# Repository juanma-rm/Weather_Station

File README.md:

# Weather Station
Weather Station is a system that senses temperature and humidity and allows checking them via Blynk (from Android app, for instance).

It is based on:
  - Wemos D1 mini ESP8266-based board, taking charge of requesting data from the sensor and sending it to a Blynk server via Wi-Fi. The device sends data for 4 seconds and goes in deep sleep mode for 5 minutes to save power.
  - DHT22 temperature and humidity sensor.
  - Blynk server to host the data.

The hardware and software diagrams, as well as the 3D view of the resulting PCB, may be found below:

* Note: Several (N) systems may be used to sense data at different points, each one requiring one DHT22 and one Wemos D1 mini
<br/>
<br/>

# Requirements
- 1 Wemos D1 mini per node
- 1 DHT22 per node
- 1 10kOhm resistor per node
- 1 microUSB charger per node
- Some way to tie and put all the previous components together (PCB + solder kit, protoboard + wires, ...)
- Blynk account + Blynk client (Android app, for instance)
- Wi-Fi available for Wemos D1 mini

# Instructions (based on my developments tools)
1) Software:
    
    1.1) Install VSCode + PlatformIO + Arduino framework + dependencies
          
          lib_deps = blynkkk/Blynk@^1.0.1<br/>
          adafruit/DHT sensor library@^1.4.2<br/>
          adafruit/Adafruit Unified Sensor@^1.1.4

    1.2) Install some Blynk client (Android app for instance), create a Blynk account and crEate your Blynk project: adding charts, labels or any other elements, creating a new device per each node selecting Wemos D1 mini, generating a token per each node and associating each charts / labels to virtual pins the devices previously created (V1 for temperature, V2 for humidity; this may be changed in main.cpp). Check out Blynk official documentation to get more details.
    
    1.3) Connect the Wemos board (without connecting it to the rest of elements).
    
    1.4) Write your device's Blynk token in auth variable, one token per node; write your WiFi credentials (ssid / pass). DEBUG macro may be uncommented to help in debugging process, if needed.
    
    1.5) Build the main.cpp (dependencies will be automatically compiled) and upload the resulting project to the board.

2) Build the hardware system:

    2.1) Order or build the PCB
    
    2.2) Mount / solder the componentes
    
    2.3) Connect the Micro-USB

3) Enjoy. If all went well, data should be now visible from the Blynk client.

# Development tools
- VSCode + PlatformIO add-on + Arduino framework
- Libraries dependencies:

          lib_deps = blynkkk/Blynk@^1.0.1<br/>
          adafruit/DHT sensor library@^1.4.2<br/>
          adafruit/Adafruit Unified Sensor@^1.1.4
          
- KiCAD for schematics and PCB layout

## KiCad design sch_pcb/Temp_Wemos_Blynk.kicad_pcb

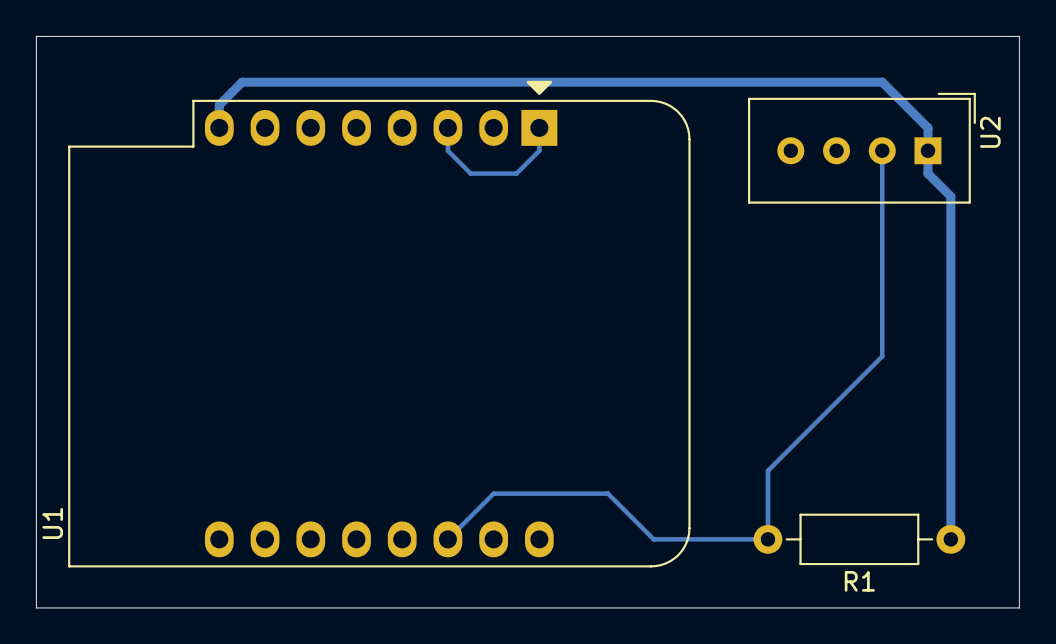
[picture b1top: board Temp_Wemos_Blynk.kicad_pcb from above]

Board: 2 copper layers, 54.6 x 31.8 mm, 3 parts (0 on the bottom side), 4 nets.

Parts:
R1: 10K; R_Axial_DIN0207_L6.3mm_D2.5mm_P10.16mm_Horizontal
U1: WeMos_D1_mini; WEMOS_D1_mini_light
U2: DHT11; Aosong_DHT11_5.5x12.0_P2.54mm

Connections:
GND: U1.10, U2.4
unnamed: R1.2, U1.14, U2.2
unnamed: U1.1, U1.3
VCC: R1.1, U1.8, U2.1

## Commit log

2023-04-15 New Blynk server version
